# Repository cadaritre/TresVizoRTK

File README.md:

# TresVizoRTK

**Alimentación — 02/10/2026:** LiPo 1S 3.7 V / 3000 mAh confirmada. Lectura MAX17048 y apagado coordinado Mk2 implementados; falta identificar el elevador de 5 V y validar físicamente el conjunto con UM980. Ver `hardware/wiring.md` desde la raíz. La carga es autónoma por hardware; USB impide el corte total de batería.
TresVizoRTK es un proyecto personal para desarrollar un prototipo funcional de receptor GNSS RTK de triple banda con IMU y lector microSD, orientado a trabajos de topografía. El repositorio reunirá el firmware de un ESP32-S3, una aplicación móvil, la documentación electrónica, la lista de materiales y los archivos mecánicos de una carcasa imprimible en 3D. La cobertura de bandas del conjunto receptor y antena deberá verificarse con el hardware real.

El objetivo es disponer de un software de instrumento robusto en el ESP32-S3, tomando la experiencia de equipos Emlid como referencia de producto. El firmware concentrará la configuración y operación del equipo; una app independiente, todavía sin iniciar, resolverá levantamientos, replanteos y trazo. Esta referencia no implica equivalencia de funciones o rendimiento validada.

El objetivo de desarrollo es alcanzar aproximadamente 2 cm de precisión en condiciones favorables. Esa cifra no representa una capacidad implementada, medida ni garantizada. La operación bajo árboles es un interés de investigación del proyecto y tampoco implica una garantía de precisión bajo vegetación.

## Estado actual

El firmware **0.8.0** está adaptado y compilado para **SparkFun Thing Plus ESP32-S3 WRL-24408**. El equipo conserva el nombre **MeridianV**, el panel, BLE, NTRIP y los servicios GNSS. La nueva placa sustituye a la Tiny; las pruebas físicas históricas de esa placa no validan este montaje.

Esta entrega añade OLED SSD1306 I2C de 128×64, microSD integrada por SDIO y una identidad de hardware independiente para las imágenes firmadas. La pantalla muestra calidad GNSS, satélites, correcciones, grabación e IP; caduca la calidad cuando dejan de llegar datos. La tarjeta no se formatea automáticamente.

El panel identifica la placa, muestra el estado de OLED y microSD y controla el registro según la disponibilidad real y el cierre de archivos. Las descargas incompletas conservan `.part`. Cargador USB y diagnóstico BLE actualizados para la nueva placa; [detalle del software](docs/panel-campo.md).

El almacenamiento se llama **Memoria interna del dispositivo** en la interfaz y en las etiquetas de la API para aplicaciones; en la OLED, **MEM INT.**. El soporte físico sigue documentado como microSD. Grabación, cierre, catálogo y descarga implementados; comprobación física pendiente.

**Pendiente de banco:** primera carga en Thing Plus, OLED recibida, microSD, enlace UART y operación prolongada. La adaptación no cargó firmware en ningún equipo. **Encendido/apagado con el SparkFun Soft Power Switch implementado; prueba física pendiente.** Durante el banco, Thing Plus y UM980 mantienen alimentación USB separada y GND común.

**Sin integrar:** IMU, radio UHF y aplicación móvil. La carcasa diseñada para Tiny requiere revisión para la Thing Plus y la OLED; no se ha dado por compatible ni se ha regenerado CAD.

El [cableado vigente](hardware/wiring.md) reúne los pines y la primera instalación. Detalle de cambios y pruebas en el [README del firmware](firmware/esp32/README.md). Las imágenes OTA llevan la [firma del propietario](tools/firmware_signing/README.md).

## Alcance previsto

El prototipo busca llegar a:

- Operación como rover RTK o como base.
- Recepción y transmisión de correcciones por los enlaces que se validen.
- Acceso a correcciones NTRIP.
- Registro de observaciones GNSS para postproceso externo.
- Integración GNSS/IMU y compensación de inclinación del jalón, todavía por desarrollar y validar.
- Configuración y operación del instrumento gestionadas por el firmware del ESP32-S3.
- Aplicación móvil independiente para levantamientos, replanteos y trazo, con acceso a configuración y estado mediante el protocolo del instrumento.
- Registro de diagnósticos para análisis y mejora del sistema.

## Arquitectura resumida

- **Receptor GNSS:** calcula la solución GNSS/RTK y produce observaciones y mensajes compatibles con su modelo y firmware.
- **ESP32-S3:** controla el receptor, enruta RTCM, adquiere la IMU, gestiona tiempos, almacenamiento, comunicaciones y apagado seguro. La fusión GNSS/IMU es trabajo futuro.
- **IMU BMI088:** aporta aceleración y velocidad angular para la futura integración GNSS/IMU y compensación de inclinación.
- **Lector y tarjeta microSD:** proporcionan almacenamiento local de observaciones, datos IMU y diagnósticos bajo control del ESP32-S3.
- **Aplicación móvil independiente:** gestiona mapas, proyectos, levantamientos, replanteos, trazo e intercambio de archivos; consulta el estado y solicita cambios de configuración al firmware.

La aplicación se comunicará mediante un protocolo propio del instrumento, separado de los comandos específicos de Unicore o u-blox. BLE se prevé como enlace principal de control y telemetría; el objetivo de 20 Hz está pendiente de pruebas. Wi-Fi, conectado al hotspot del teléfono, permitiría al ESP32 acceder a NTRIP. USB se reserva para desarrollo y diagnóstico, y Wi-Fi o USB para transferencias grandes.

La [arquitectura](docs/architecture.md) describe las responsabilidades y los flujos de datos con mayor detalle.

## Hardware previsto

La base considerada incluye:

- Unicore UM980 en una placa de desarrollo o carrier como GNSS principal.
- u-blox ZED-F9P disponible para posibles pruebas.
- SparkFun Thing Plus ESP32-S3 WRL-24408, con 4 MB de flash y 2 MB de PSRAM Quad según fabricante.
- Bosch BMI088 en breakout.
- Socket microSD integrado de la Thing Plus, SDIO de cuatro bits y tarjeta FAT32.
- OLED Tecneu 0.96 pulgadas I2C, cuatro pines y 128×64; driver SSD1306 según referencia del vendedor.
- Antena Helix, cuya compra confirmó el propietario; modelo y bandas por verificar. La HA-901A mencionada inicialmente no está confirmada.
- Batería LiPo de una celda, nominal 3.7 V y 3000 mAh, confirmada por el propietario.
- SparkFun Soft Power Switch JST 2 mm comprado; integración de encendido/apagado implementado; prueba física pendiente.
- Carcasa cilíndrica impresa en 3D y montaje sobre jalón.

El enlace GNSS usa RX del ESP32 en **GPIO44** y TX en **GPIO43**, con GND común; ambos equipos reciben alimentación USB por separado. La OLED usa **SDA8/SCL9 y 3.3 V**. El pinout de la Tiny (18/17) queda como historial. La disponibilidad de PPS en la carrier UM980 concreta está pendiente de verificación. Consulta la [lista de materiales](hardware/bom.md) y el [cableado vigente](hardware/wiring.md).

## Mapa del repositorio

| Ruta | Contenido previsto |
| --- | --- |
| `firmware/esp32/` | Firmware del controlador ESP32-S3. |
| `app/` | Aplicación móvil del instrumento. |
| `hardware/` | BOM, módulos comerciales, conexiones y referencias del hardware vigente. |
| `mechanical/` | V1 para imprimir y fuentes necesarias para regenerarla. |
| `docs/` | Arquitectura, estado, hoja de ruta y entorno de desarrollo. |
| `tools/` | Puente USB, diagnóstico GNSS/BLE, empaquetado y actualización de firmware. |
| `tests/fixtures/` | Datos de prueba pequeños y anonimizados. |

## Documentación

- [Arquitectura del sistema](docs/architecture.md)
- [Estado del proyecto](docs/project-status.md)
- [Servicios actuales del ESP32 (0.5.0)](docs/esp32-services.md)
- [Configuración avanzada del receptor (0.6.0)](docs/gps-advanced.md)
- [Panel reorganizado para campo (0.6.0)](docs/panel-campo.md)
- [Hoja de ruta](docs/roadmap.md)
- [Entorno y prácticas de desarrollo](docs/development.md)
- [Lista de materiales](hardware/bom.md)
- [Identificación del hardware recibido](hardware/identification.md)
- [Interfaces y conexiones](hardware/wiring.md)
- [Mecánica vigente, V2.2](mechanical/README.md)
- [Auditoría de la carcasa V1](mechanical/AUDITORIA-V1.md)
- [BOM de tornillería](mechanical/v2.2/SCREW-BOM.md)
- [Revisión de integración de V1, antecedente](docs/INTEGRATION_REVIEW.md)

No se ha seleccionado una licencia. El contenido del repositorio no debe interpretarse como publicado bajo una licencia específica hasta que el propietario la defina expresamente.

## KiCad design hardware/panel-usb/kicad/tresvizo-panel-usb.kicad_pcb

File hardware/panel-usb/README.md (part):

# Placa del USB-C del panel (TresVizo MeridianV, exploratoria v0.1)

> **En la v0.3 (rama `hw/compact-v03`) esta placa no se usa:** el USB-C va en la placa principal
> ([../main-board](../main-board/README.md)).

> **Estado:** diseño generado con scripts y revisado con el ERC y el DRC de KiCad 10.0.6.
> **No se ha fabricado ni probado.** Vive en la rama `hw/main-board-kicad`, junto a la placa principal
> ([../main-board](../main-board/README.md)), y se pide en el mismo panel de JLCPCB que ella.

## Para qué sirve

Lleva un receptáculo USB-C 2.0 al ras de la cara exterior de la tapa curva del panel de la carcasa
V2.2 y lo une con un cable corto JST GH de 8 pines a J101 de la placa principal (carga a 5 V y
USB nativo del ESP32-S3). Es una placa de 4 capas y 1.6 mm, con todas las piezas por la cara superior.

Esquema en [fab/tresvizo-panel-usb-schematic.pdf](fab/tresvizo-panel-usb-schematic.pdf) y vistas en
[fab/tresvizo-panel-usb-top.png](fab/tresvizo-panel-usb-top.png) /
[fab/tresvizo-panel-usb-bottom.png](fab/tresvizo-panel-usb-bottom.png). Los genera `build.py`, igual que el ZIP
de Gerber: cambian en cada vuelta y solo se guardan en git en los hitos (`git add -f`).

## Circuito

| Ref. | Pieza | Función |
| --- | --- | --- |
| J501 | HRO TYPE-C-31-M-12 (USB-C 16 contactos, horizontal) | A6/B6 = D+ y A7/B7 = D− unidos en la placa; SBU sin conectar; carcasa a GND |
| R501, R502 | 5.1 kΩ 0402 | Rd de CC1 y CC2 a GND: el cargador ve un sumidero y entrega 5 V |
| U501 | USBLC6-2SC6 (UMW) | ESD de D+/D−; pin 5 a VBUS y pin 2 a GND |
| D501 | SMF15A (SOD-123FL) | TVS unidireccional de VBUS (la misma pieza que usa la placa principal) |
| J502 | JST GH 8 lateral, XUNPU WAFER-GH1.25-8PWB | Cable a J101 de la placa principal |

Redes: VBUS, GND, USB_DP, USB_DN, CC1, CC2. VBUS se queda en 5 V: solo hay Rd (sin PD) y el cargador
BQ25798 de la placa principal no tiene conectados sus D+/D− (sin HVDCP), así que el pin 5 del USBLC6
puede ir a VBUS.

Detalles de la placa:

- **Cruce de D+/D−.** En el receptáculo los contactos quedan D+, D−, D+, D− (B6, A7, A6, B7). D+ se une
  por la capa superior con una U que rodea la vía de A7; D− se une por la capa inferior y vuelve arriba
  debajo de la U. Desde ahí el par va a 0.25 mm con 0.2 mm entre pistas.
- **U501 cerca de J502.** D+ atraviesa el USBLC6 (pin 6 → pin 1, bajo el cuerpo) y entra a J502.8; D− le
  llega con un ramal de unos 4.5 mm por la capa inferior. Entre J501 y U501 hay unos 10 mm de pista:
  junto al receptáculo no cabía con el cruce, las Rd y VBUS. La placa principal tiene su propio USBLC6
  (U101) junto a J101.
- **VBUS (≥ 0.6 mm).** Cada pad de VBUS del USB-C baja por dos vías a una pista de 0.8 mm en la capa
  inferior, que sube por tres vías a los pines 1-3 de J502. D501 va junto a J502.1. Así VBUS cruza por
  debajo del par de datos sin cortar nada.
- **GND.** Rellenos de GND en las cuatro capas (las internas enteras), 18 vías de cosido y 9 vías de
  bajada de pads (fanout). Los pads de GND del USB-C y las Rd van directo a las patas de la carcasa.
  Todas las vías van tapadas por las dos caras.

## Elección del receptáculo

Se compararon los planos de los dos candidatos (stock de la API de JLCPCB del 04-10-2026):

| | HRO TYPE-C-31-M-12 (C165948) | SHOU HAN TYPE-C 16PIN 2MD(073) (C2765186) |
| --- | --- | --- |
| Stock / precio unitario | 424 026 / 0.19 USD | 882 909 / 0.07 USD |
| Valores nominales | 20 V, 5 A | 5 V, 3 A |
| Canto de la placa | **Dibujado** («PCB EDGE»): 5.79 mm por delante de los postes de centrado | No lo da: su «PRODUCT EDGE» es el frente del propio conector |
| Cara de acoplamiento | 6.28 mm por delante de los postes (2.60 mm por delante de las patas delanteras) → **sobresale 0.49 mm** del canto dibujado | 6.28 mm por delante de los postes; sin referencia al canto |
| Altura del eje | No acotada; altura total 3.26 mm | No acotada; altura total 3.16 mm |

Se eligió el **HRO TYPE-C-31-M-12**: su plano fija la cara respecto del canto. Ningún plano acota la
altura del eje. El modelo 3D de LCSC tiene la carcasa de 0.05 a 3.25 mm sobre la placa, lo que pone el
eje a **1.65 mm**. Concuerda con la altura total de 3.26 mm del plano y con la vista frontal medida a
escala (1.65-1.69 mm).

La huella sale de LCSC/EasyEDA (orientación de JLCPCB), con estos ajustes (ver `scripts/mklib.py`):

- pads dobles separados por contacto;
- ranuras de la carcasa con las medidas del plano (0.6 × 1.7 y 0.6 × 1.4 mm), anillo de 0.2 mm y pasta;
- postes de centrado sin metalizar;
- modelo 3D corrido 2.22 mm, porque el de EasyEDA quedaba fuera de sus ranuras (comprobado en la
  exportación VRML).

## Mecánica

Ejes de la carcasa V2.2 (del estudio CAD): z = eje del jalón hacia arriba, +Y hacia el panel, +X a la
izquierda mirando el panel. La placa es horizontal: cara inferior en z = 90.17 y cara de componentes en
z = 91.77, hacia arriba. Coordenadas de la placa, vista desde arriba con el USB-C arriba:
**u = x + 10.4**, **v = 31.3 − y**.

- **Contorno:** cuerpo u 0–20.8, v 4.7–19.8; lengüeta frontal u 5.2–15.6, v **0.89**–4.7; esquinas de
  R0.5.
  - **El USB-C sobresale 1.29 mm** del frente de la lengüeta (decisión del propietario del
    05-10-2026). El frente quedó 0.8 mm más atrás que el canto del plano de HRO: v = 0.89
    (y = 30.41). La cara sigue en v = −0.40.
  - El cobre más cercano al frente es el de las ranuras delanteras de la carcasa del USB-C, a
    0.41 mm (la regla pide 0.3 mm). Los rellenos de GND paran a 0.3 mm.
  - Los agujeros no cambian: están en el cuerpo, a 0.5 mm de su canto delantero (v 4.7) y a 1.4 mm
    de los laterales.
- **J501:** centrado en u = 10.4 (x = 0), **cara en v = −0.40 (y = 31.70)**, a ras de la tapa curva.
  **Eje a 1.65 mm de la cara de componentes → z = 93.42** (el estudio buscaba 93.50; la abertura de la
  tapa está centrada en z = 93.2 con ±3.5 mm). Carcasa de x = ±4.47, z 91.82–95.02.
- **Agujeros:** H501 y H502, M2 sin metalizar de Ø2.2 en (u, v) = (2.5, 6.3) y (18.3, 6.3), es decir
  x = ∓7.9, y = 25.0, sin cobre en Ø4.4.
- **J502 (GH 8):** en el canto trasero con la boca hacia −Y. Pines 1-8 de izquierda a derecha (u 6.02 a
  14.77), pads en v 14.07–15.77, cuerpo en v 15.5–19.5 y 4.35 mm de alto (llega a z = 96.12).
  - Los anclajes llegan hasta v 19.48 para dejar 0.3 mm de cobre al canto.
  - El plano de XUNPU pone el frente del cuerpo a ras del extremo de los anclajes, y el modelo 3D de
    LCSC 0.09 mm más afuera: la boca queda 0.23–0.32 mm dentro del canto.
  - El GH original de JST dibuja los anclajes 0.25 mm por delante del cuerpo.
- **Resto de piezas:**

  | Ref. | (u, v) | Por qué |
  | --- | --- | --- |
  | R501 | (14.0, 9.75) | Dentro de la zona prevista |
  | R502 | (6.8, 9.75) | Dentro de la zona prevista |
  | U501 | (17.1, 13.4) | Fuera de la zona: con el GH los pads de J502 empiezan en v = 14.07 y queda sitio debajo |
  | D501 | (3.4, 13.0) | Fuera de la zona, junto a J502.1 |

  Todo queda a más de 1 mm de los agujeros (la zona sin cobre es de Ø4.4) y de los cantos laterales.
- **Puentes del panel:** uno en cada canto lateral (u = 0 y u = 20.8), centrados en v = 16.0, de 5 mm.
  - Medido desde la esquina superior izquierda del rectángulo que encierra la placa (u 0, v 0.89):
    **canto izquierdo y canto derecho, a 15.11 mm**.
  - Zona sin cobre de 1 mm de fondo en v 13.0–19.0.
  - El canto trasero no sirve: allí están la boca y los anclajes de J502.
  - En el panel, el USB-C asoma 1.29 mm sobre la fresa. Con la fresa normal de 2 mm quedaría a
    0.71 mm del marco. Por eso, frente a la lengüeta, la fresa del panel se ensancha a 3 mm y quedan
    **1.71 mm** (`cuts` en `../main-board/kicad/panel.json`).

`fab/check3d.txt` (lo escribe `build.py`) mide estas posiciones sobre los modelos 3D de la placa armada.

### Cambios que necesita la tapa del panel del V2.2 (solo propuesta; no se tocó el CAD)

- Quitar el bolsillo del JST-XH.
- Abrir un hueco de 12.8 × 7.0 mm con radios de 1.2 mm, centrado en x = 0, z = 93.2.
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
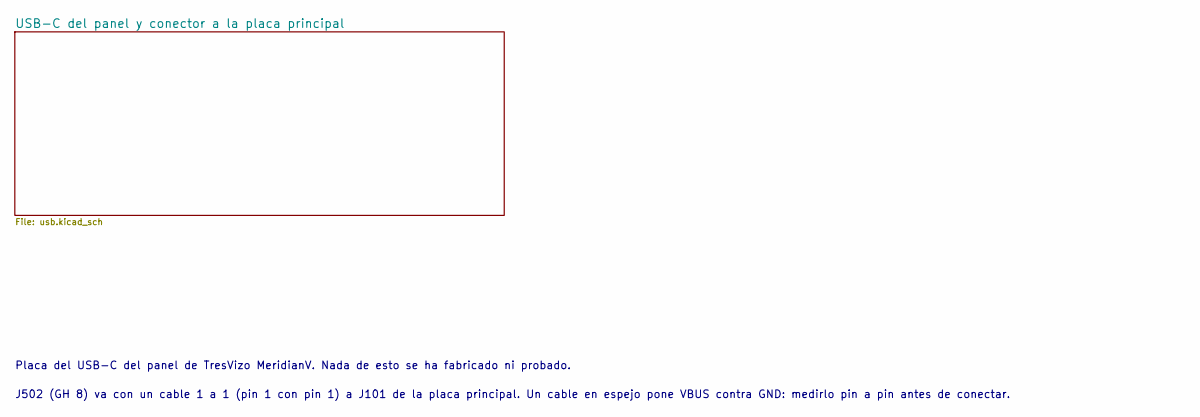
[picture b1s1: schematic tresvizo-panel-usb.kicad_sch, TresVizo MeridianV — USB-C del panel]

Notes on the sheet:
Placa del USB-C del panel de TresVizo MeridianV. Nada de esto se ha fabricado ni probado.
J502 (GH 8) va con un cable 1 a 1 (pin 1 con pin 1) a J101 de la placa principal. Un cable en espejo pone VBUS contra GND: medirlo pin a pin antes de conectar.

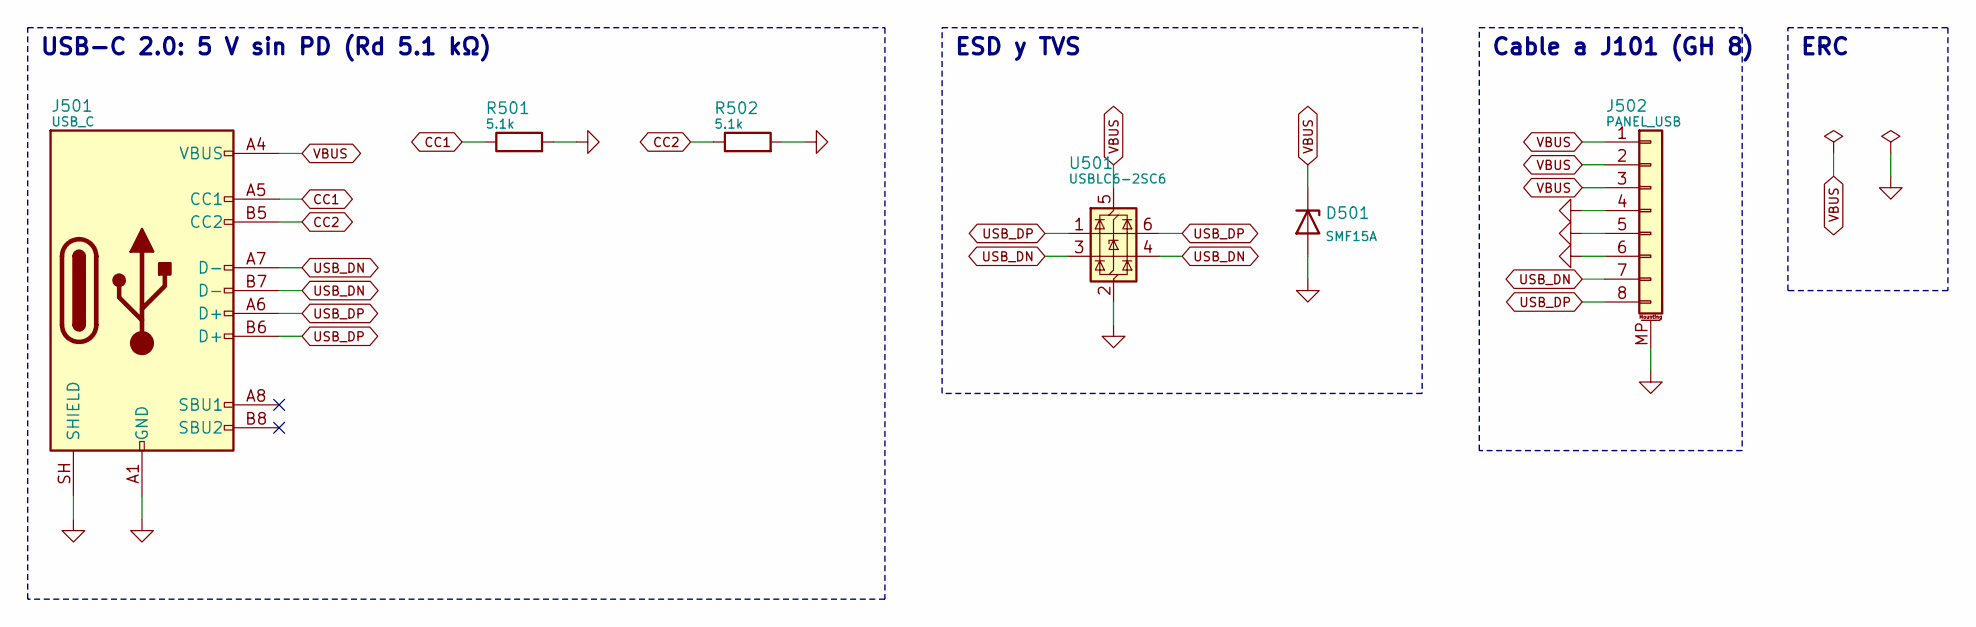
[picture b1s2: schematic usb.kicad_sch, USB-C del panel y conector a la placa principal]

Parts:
D501: SMF15A; SOD-123FL_L2.7-W1.8-LS3.8-RD; MPN SMF15A; LCSC C19077509
J501: USB_C; USB-C_SMD-TYPE-C-31-M-12; MPN TYPE-C-31-M-12; LCSC C165948
J502: PANEL_USB; CONN-SMD_8P-P1.25_XUNPU-WAFER-GH1.25-8PWB; MPN WAFER-GH1.25-8PWB; LCSC C3029383
R501, R502: 5.1k; R_0402_1005Metric; MPN 0402WGF5101TCE; LCSC C25905
U501: USBLC6-2SC6; SOT-23-6_L2.9-W1.6-P0.95-LS2.8-BL; MPN USBLC6-2SC6; LCSC C2687116

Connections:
CC1: J501.A5 (CC1), R501.1
CC2: J501.B5 (CC2), R502.1
GND: D501.2 (A), J501.A1 (GND), J501.A12 (GND), J501.B1 (GND), J501.B12 (GND), J501.SH (SHIELD), J502.4, J502.5, J502.6, J502.MP (MountPin), R501.2, R502.2, U501.2 (GND)
USB_DN: J501.A7 (D-), J501.B7 (D-), J502.7, U501.3 (I/O2), U501.4 (I/O2)
USB_DP: J501.A6 (D+), J501.B6 (D+), J502.8, U501.1 (I/O1), U501.6 (I/O1)
VBUS: D501.1 (K), J501.A4 (VBUS), J501.A9 (VBUS), J501.B4 (VBUS), J501.B9 (VBUS), J502.1, J502.2, J502.3, U501.5 (VBUS)

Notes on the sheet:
USB-C 2.0: 5 V sin PD (Rd 5.1 kΩ)
ESD y TVS
Cable a J101 (GH 8)
ERC

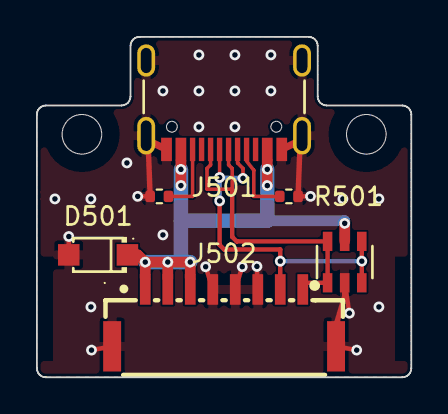
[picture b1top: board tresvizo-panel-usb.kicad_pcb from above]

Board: 4 copper layers, 20.8 x 18.9 mm, 8 parts (0 on the bottom side), 6 nets.

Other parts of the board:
H501, H502: MountingHole_2.2mm_M2

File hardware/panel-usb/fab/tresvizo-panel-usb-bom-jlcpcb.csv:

Comment,Designator,Footprint,LCSC Part #
SMF15A,D501,SOD-123FL_L2.7-W1.8-LS3.8-RD,C19077509
USB_C,J501,USB-C_SMD-TYPE-C-31-M-12,C165948
PANEL_USB,J502,CONN-SMD_8P-P1.25_XUNPU-WAFER-GH1.25-8PWB,C3029383
5.1k,"R501,R502",R_0402_1005Metric,C25905
USBLC6-2SC6,U501,SOT-23-6_L2.9-W1.6-P0.95-LS2.8-BL,C2687116

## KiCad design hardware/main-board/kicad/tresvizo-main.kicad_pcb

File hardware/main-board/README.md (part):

# Placa principal TresVizo MeridianV (exploratoria, v0.3 compacta)

> **Estado:** diseño generado con scripts y revisado con el ERC y el DRC de KiCad 10.0.6 y con una
> auditoría eléctrica independiente (08-10-2026), cuyos cambios ya están aplicados. **No se ha
> fabricado ni probado.** Vive en la rama `hw/compact-v03`, fuera de `main`, porque el propietario la
> pidió como exploración (07-10-2026). Los resultados de las comprobaciones están en
> [Verificaciones](#verificaciones).
>
> La v0.2 (placa de 46 × 64 mm más la panel-usb, para la carcasa V2.3) sigue en la rama
> `hw/main-board-kicad`.

La v0.3 es la versión compacta del receptor. Mantiene el concepto de la v0.2: el UM980 en su
carrier BDLX, por cable, y el ESP32-S3-WROOM-1 en la placa. Pero va en un tubo de **Ø56 × 116** con
una cara plana al frente ([carcasa V3.0](../../mechanical/v3.0/README.md)). La placa mide
**36 × 71.5 mm** (4 capas, 1.6 mm, componentes solo por la cara de arriba) y lleva lo que en la v0.2
iba en el panel: el USB-C, la OLED (soldada a la placa), un pulsador y un LED de estado. El BMI088
vuelve a la placa. No hay panel-usb: la placa se pide sola, en un panel de JLCPCB con un BOM y un
CPL. La batería pasa a un pack comercial 1S2P de dos 18650.

| Bloque | Pieza | Notas |
| --- | --- | --- |
| GNSS | Carrier BDLX RTK_UM98_V1.0.1, fuera de la placa | J301 (SH de 8 pines): COM2 a 115200, PPS, EVENT, RESET_N y su 5 V. Arnés soldado a la carrier |
| 5 V del GNSS | TI TPS63070 (buck-boost) | 4.88 V desde VSYS; GPIO45 lo enciende; apagado desconecta la carga |
| MCU | ESP32-S3-WROOM-1-N16R2 | 16 MB de flash y 2 MB de PSRAM quad. Antena hacia el canto −X. Mismos GPIO que la v0.2, salvo GPIO48 (ver [Firmware](#firmware-qué-tiene-que-cambiar)) |
| IMU | Bosch BMI088 en la placa (U401) | I2C en un segundo bus (GPIO41/42), INT1 en GPIO2 e INT3 en GPIO1; 0x18 y 0x68 |
| Registro | microSD de empuje TF-015 (J401), SD_MMC 4 bits | CLK GPIO6, CMD 7, D0 5, D1 4, D2 16, D3 15 y detección en 17 (HIGH con tarjeta). Boca hacia el costado +X |
| USB-C | HRO TYPE-C-31-M-12 (J101) | Rd de 5.1 kΩ en CC1 y CC2, TVS SMF15A en VBUS y USBLC6 (U101) en D+/D−. Boca hacia el costado +X |
| Carga | TI BQ25798 (buck-boost NVDC) | USB-C a 5 V, techo de entrada ~1.45 A (ILIM); 1S; usar y cargar a la vez. Carga de 1 A por omisión; el firmware no debe pasar de 1.5 A |
| Apagado | Modo *ship* del cargador + FET externo | El pulsador despierta la placa (QON) |
| 3.3 V | TI TPS62903 | 3–17 V, 3 A, modo 100 % |
| Medidor | MAX17048 | I2C 0x36 |
| Interfaz | OLED 0.96" de 4 pines (J403), pulsador SW401 y LED rojo D403 | La OLED es la del propietario y la suelda él sobre pads SMD. El LED va en GPIO48 |
| Batería | Pack 1S2P (2 × 18650 en paralelo) por J102 (GH de 4 pines) | NTC 10k B3435 obligatoria por J404 (SH de 2 pines) |

Esquema en [fab/tresvizo-main-schematic.pdf](fab/tresvizo-main-schematic.pdf), mapa de pines y
conectores en [fab/pinout.md](fab/pinout.md) y vistas en `fab/*-top.png` / `fab/*-bottom.png`. La
especificación de la v0.3, la colocación, las desviaciones, el ruteo y la auditoría eléctrica están
en [research/v03-compacta.md](research/v03-compacta.md); la investigación de la v0.2, en
[research/v02.md](research/v02.md). El esquema en PDF, las vistas y los Gerber los genera
`build.py` y solo se guardan en git en los hitos (ver [Regenerar](#regenerar)).

## Decisiones

### De la v0.3 (07-10-2026 y auditoría del 08-10-2026)

Pedido del propietario: un receptor más chico, con el panel dentro de la placa principal, dos 18650
y la carrier tal cual. Lo que resultó al aplicarlo, con su motivo:

1. **Tubo de Ø56 × 116 y placa de 36 × 71.5 mm.** Unos dos tercios del volumen de V2.3.
   - Empezó en Ø52 × 100. El endurecimiento del 08-10-2026 lo agrandó para dejar holguras de
     impresión y de montaje, y el coaxial con curvas de R 12 o más (ver [Mecánica](#mecánica)); la
     placa no cambió de lugar.
   - Los cantos laterales corren por los rieles del chasis, con una franja de 1 mm sin componentes.
   - Componentes solo por la cara de arriba: el dorso mira a la carrier a 0.5 mm.
   - El alto de cada pieza lo limitan la curva del tubo y la cara plana.
   - Dos muescas en el contorno: la clavija del SMA de la carrier y la funda de la clavija del USB-C.
   - Ver [Mecánica](#mecánica).
2. **El panel entra en la placa.** Motivos: no hay cables al panel y el botón metálico de 12 mm de
   la v0.2 es difícil de conseguir.
   - USB-C J101 (TYPE-C-31-M-12, C165948, el de la panel-usb): Rd de 5.1 kΩ en CC1 y CC2 (R119,
     R120), TVS SMF15A en VBUS y USBLC6 (U101) junto al conector.
   - Pulsador táctil SW401 (TS-1187A-B-A-B, 5.1 × 5.1 × 1.5 mm) a BTN_N: despierta al cargador (QON)
     y llega a GPIO18 por D402. Conserva la ESD D401, porque la tecla deja llegar descargas a su botón
     de latón.
   - LED de estado D403 (0603 rojo) directo desde GPIO48, con 330 Ω: unos 4.4 mA. Con 1 kΩ quedaba
     tenue detrás de la guía de luz (auditoría). R409 era la resistencia del anillo del botón.
   - Se van J101 GH 8 (USB del panel), J402 (botón), J405 (IMU por cable), Q402 y R410 (anillo del
     botón). J403 sigue, ahora como huella del módulo OLED. Los números R106 y R410 quedan sin usar,
     para no renumerar.
3. **OLED soldada a la placa (J403).** Es el mismo módulo I2C de 4 pines que ya tiene el propietario.
   - Va girado 180° (pines abajo), sobre separadores de 1.3 mm, con el vidrio detrás de la ventana de
     la cara plana. Sobresale por encima del canto de arriba de la placa.
   - **Pads SMD de 1.7 × 2.4 mm, sin agujeros** (auditoría). Detrás de la fila de pines está el SMA
     de la carrier, a 0.4 mm del dorso, y una soldadura pasante recortada podía cortocircuitar +3V3 y
     SCL con su carcasa (GND).
   - La única unión pasante de la placa son las cuatro patas de la carcasa del USB-C (GND), que no
     salen por detrás.
   - JLCPCB no monta la OLED: sus pads llevan pasta y salen estañados. El propietario corta los pines
     a la altura del separador y los suelda sobre los pads calentando desde el frente del módulo.
4. **BMI088 en la placa (U401)**, como en v0.1, en el bus que usaba J405. No hacen falta cable ni
   plataforma, y queda rígido con el resto del equipo.
   - Conexión según la hoja de Bosch (BST-BMI088-DS001 rev 1.9): PS a VDDIO (I2C), CSB1 a VDDIO y
     CSB2 al aire.
   - SDO1 y SDO2 a GND: acelerómetro 0x18 y giróscopo 0x68, las direcciones del breakout de la v0.2.
   - INT2 e INT4 sin conectar, 100 nF en VDD y en VDDIO, pull-ups de 4.7 kΩ y sin cobre de la cara
     de arriba bajo el encapsulado (DS §8.2).
   - Sigue en un **segundo bus** (GPIO41 SDA, GPIO42 SCL, 400 kHz), aparte del de la OLED, el
     cargador y el medidor, y con sus dos interrupciones.
   - Va en la esquina de abajo a la izquierda, lejos de L101, del botón y de los puentes del panel.
5. **Pack 1S2P por un GH 4 (J102).** El PH 2 lateral de la v0.2 mide 5.5 mm sobre la placa y aquí
   caben unos 4.6.
   - JST GH 4 lateral (SM04B-GHS-TB, C189895, unos 4.25 mm de alto) con dos contactos por polo: 1 y
     2 a GND, 3 y 4 a VBATT_IN.
   - JST da 1 A por contacto con cable AWG #26: unos 2 A por polo. El firmware limita la carga a
     1.5 A como mucho (ver [Firmware](#firmware-qué-tiene-que-cambiar)).
6. **Conectores de cable solo en el canto de abajo**, con la boca hacia abajo: a los lados no hay
   sitio para las clavijas. Son J404 (NTC), J102 (batería) y J301 (GNSS), y se alcanzan quitando la
   base.
7. **La carrier BDLX tal cual**, con el arnés soldado a sus filas de agujeros, como en la v0.2. Sus
   agujeros solo se conocen a ±1 mm (foto): una mezzanine pediría medidas exactas.
8. **Antena del ESP32 hacia el canto −X**, con un área sin pistas, vías ni rellenos en las cuatro
   capas que la auditoría amplió (ver
   [research/v03-compacta.md](research/v03-compacta.md#colocación)).
9. **Resto de la auditoría eléctrica** (detalle en
   [research/v03-compacta.md](research/v03-compacta.md#auditoría-eléctrica-08-10-2026)):
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
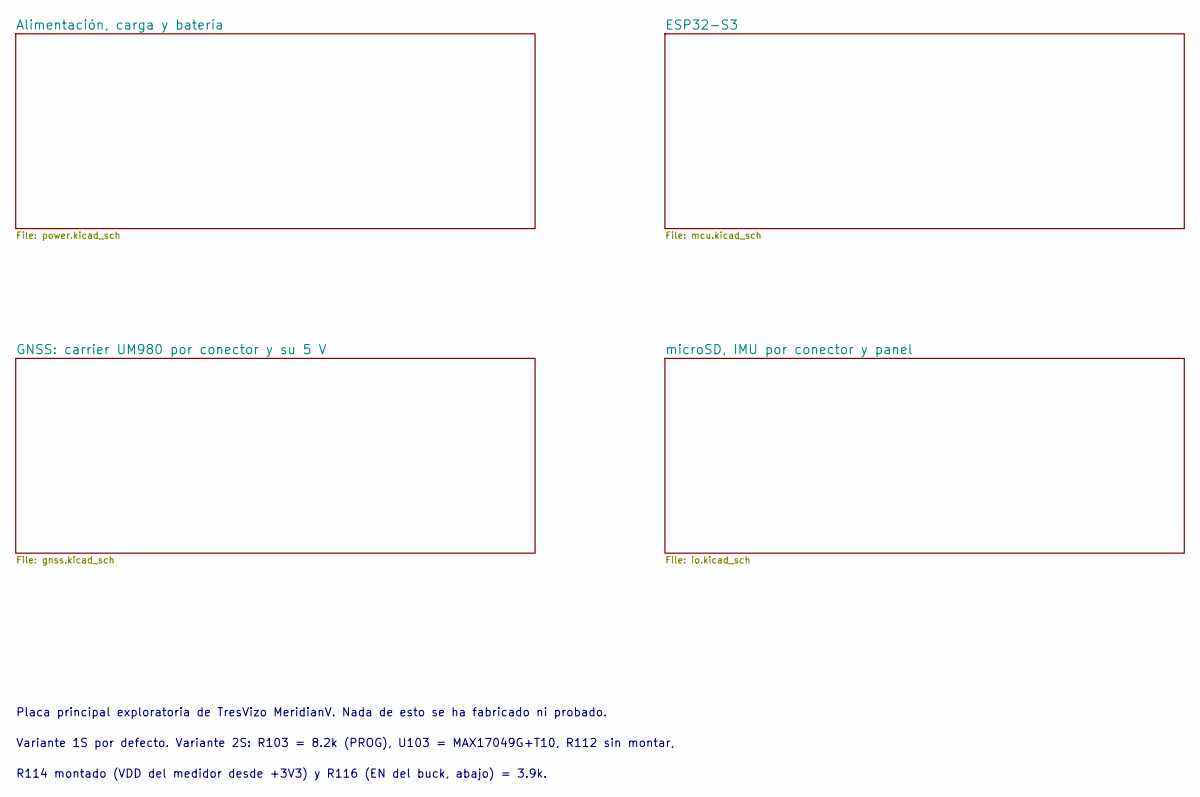
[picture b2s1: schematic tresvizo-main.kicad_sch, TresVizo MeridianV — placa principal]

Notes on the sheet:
Placa principal exploratoria de TresVizo MeridianV. Nada de esto se ha fabricado ni probado.
Variante 1S por defecto. Variante 2S: R103 = 8.2k (PROG), U103 = MAX17049G+T10, R112 sin montar,
R114 montado (VDD del medidor desde +3V3) y R116 (EN del buck, abajo) = 3.9k.

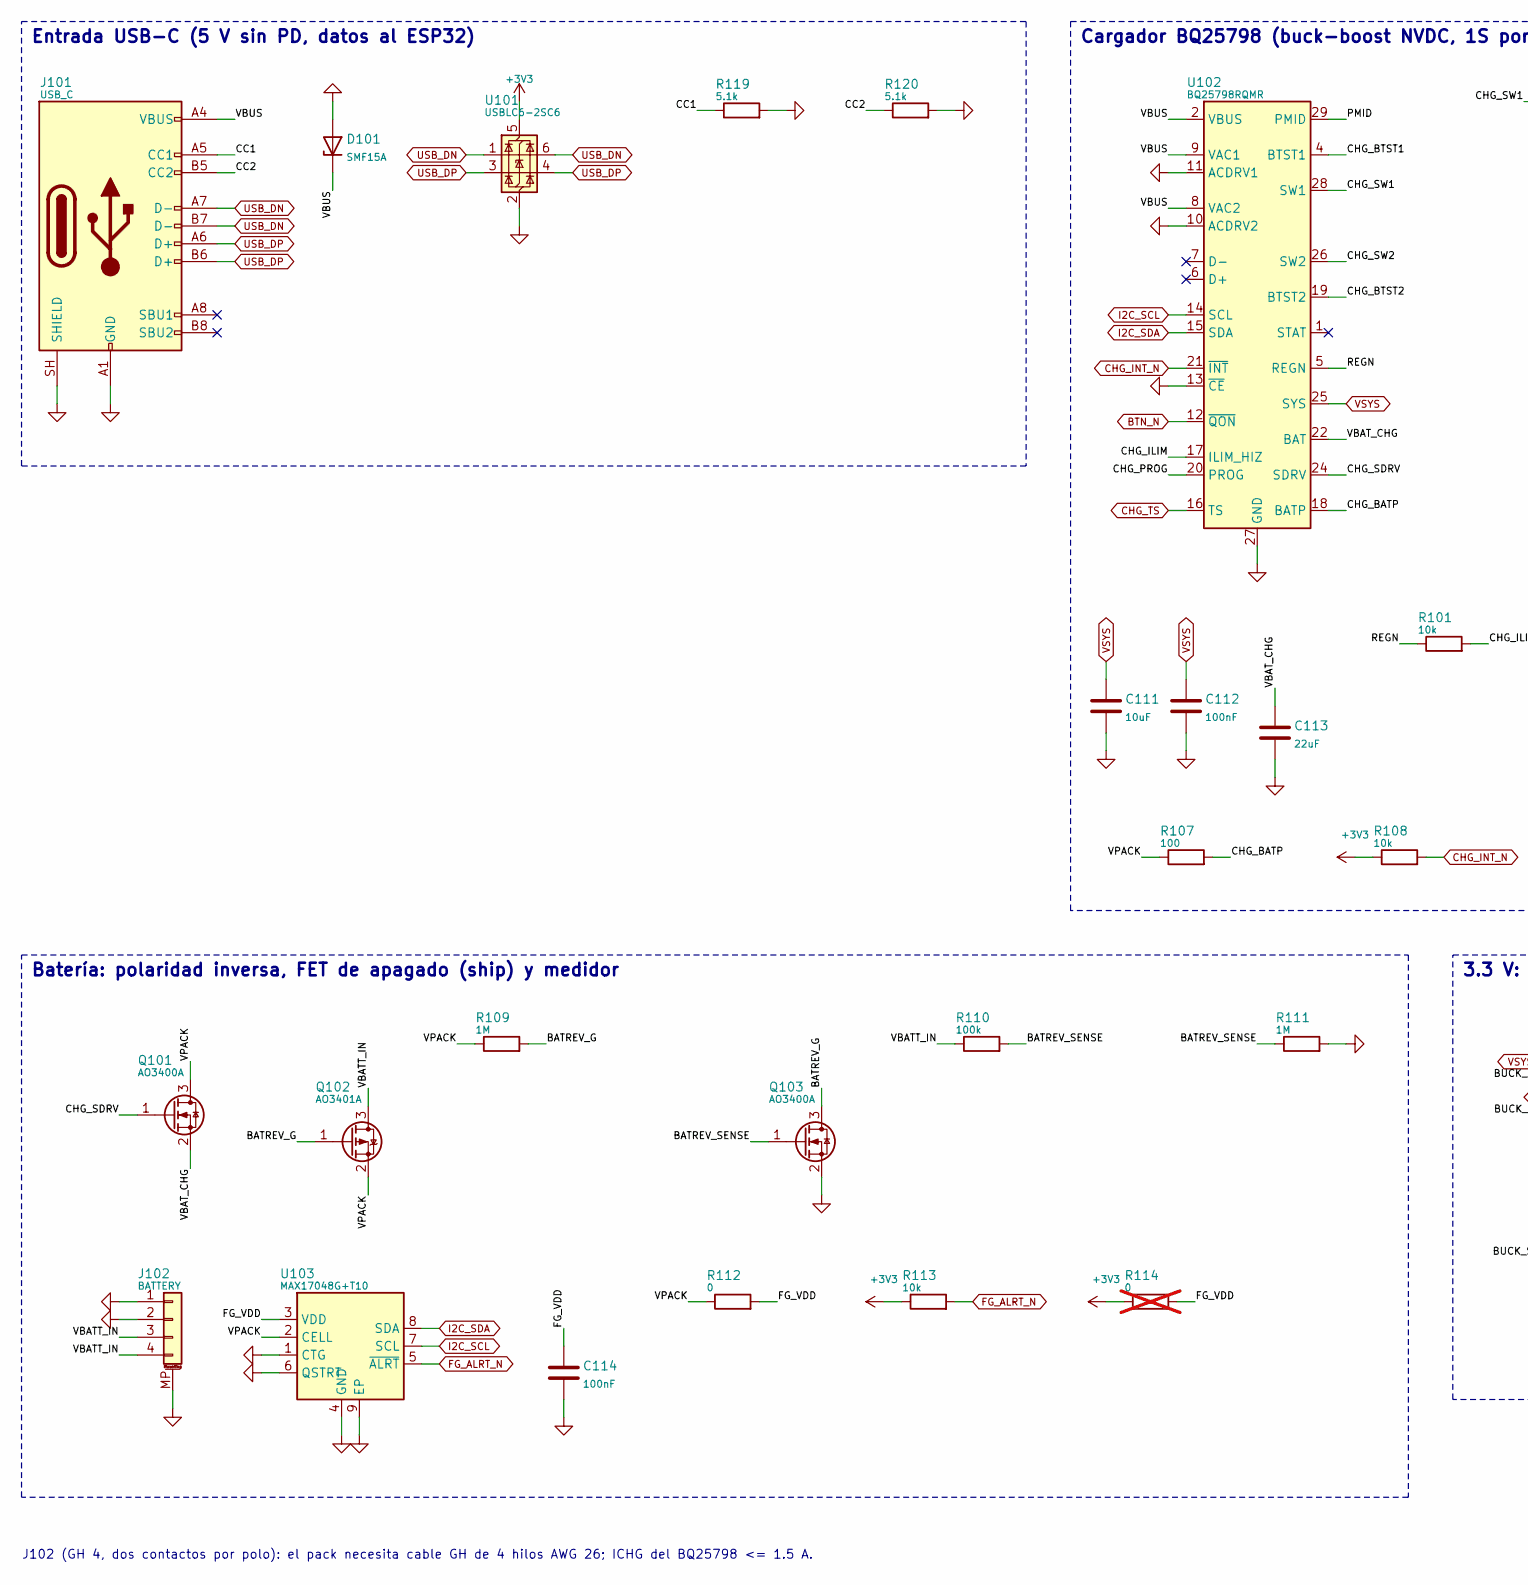
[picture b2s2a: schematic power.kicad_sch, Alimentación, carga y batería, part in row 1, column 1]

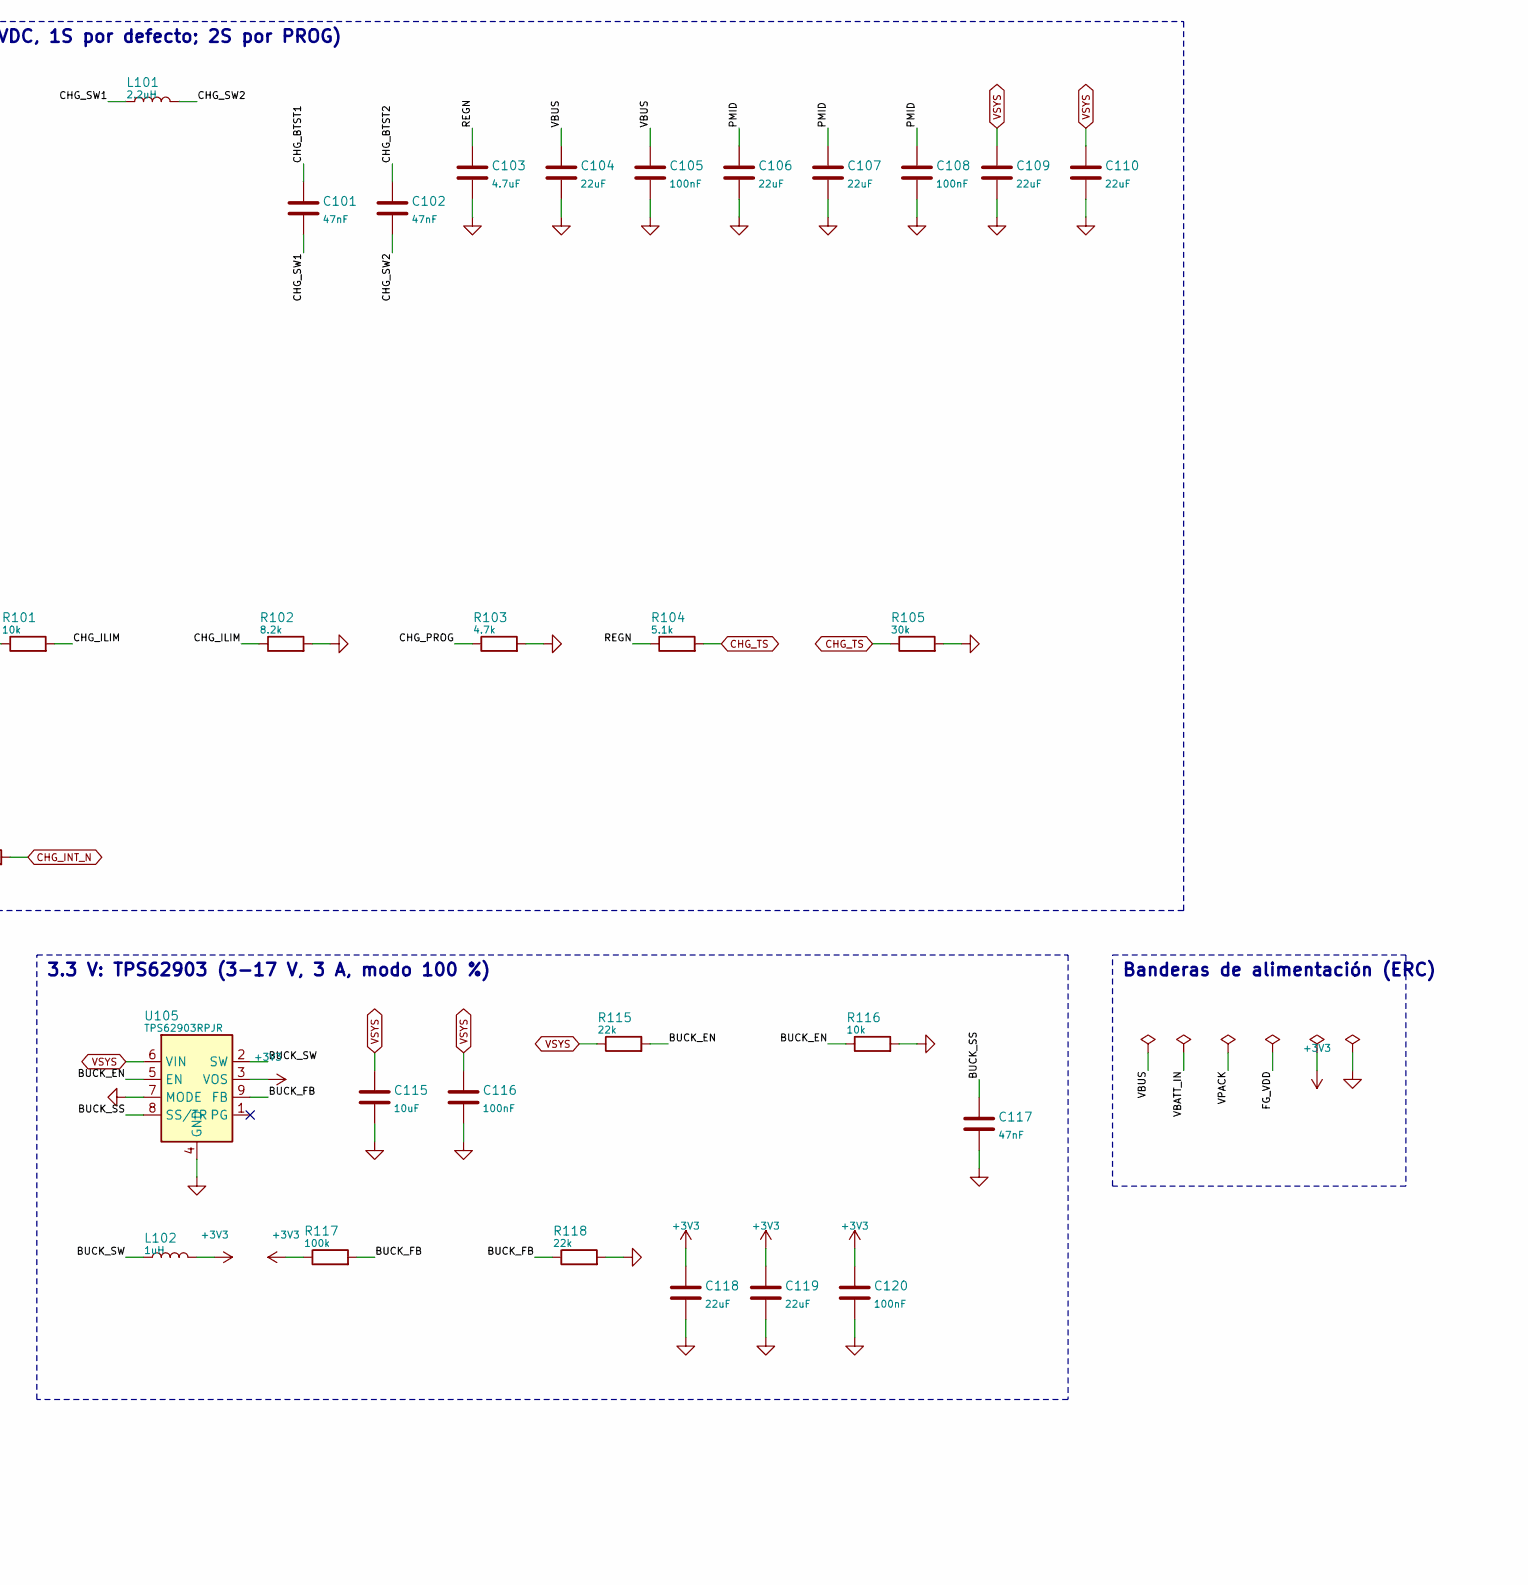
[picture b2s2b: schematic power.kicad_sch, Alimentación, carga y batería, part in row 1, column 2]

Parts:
C101, C102, C117: 47nF; C_0603_1608Metric; MPN CL10B473KB8NNNC; LCSC C1622
C103: 4.7uF; C_0603_1608Metric; MPN CL10A475KO8NNNC; LCSC C19666
C104, C106, C107, C109, C110, C113, C118, C119: 22uF; C_0805_2012Metric; MPN CL21A226MAQNNNE; LCSC C45783
C105, C108, C112, C114, C116, C120: 100nF; C_0402_1005Metric; MPN CL05B104KB54PNC; LCSC C307331
C111, C115: 10uF; C_0805_2012Metric; MPN CL21A106KAYNNNE; LCSC C15850
D101: SMF15A; SOD-123FL_L2.7-W1.8-LS3.8-RD; MPN SMF15A; LCSC C19077509
J101: USB_C; USB-C_SMD-TYPE-C-31-M-12; MPN TYPE-C-31-M-12; LCSC C165948
J102: BATTERY; CONN-SMD_4P-P1.25_SM04B-GHS-TB-LF-SN; MPN SM04B-GHS-TB(LF)(SN); LCSC C189895
L101: 2.2uH; IND-SMD_L5.4-W5.2; MPN MWSA0503S-2R2MT; LCSC C408408
L102: 1uH; L2520; MPN DFE252012F-1R0M=P2; LCSC C435392
Q101, Q103: AO3400A; SOT-23-3_L2.9-W1.3-P1.90-LS2.4-BR; MPN AO3400A; LCSC C20917
Q102: AO3401A; SOT-23_L2.9-W1.3-P1.90-LS2.4-BR; MPN AO3401A; LCSC C15127
R101, R108, R113, R116: 10k; R_0402_1005Metric; MPN 0402WGF1002TCE; LCSC C25744
R102: 8.2k; R_0402_1005Metric; MPN 0402WGF8201TCE; LCSC C25924
R103: 4.7k; R_0402_1005Metric; MPN 0402WGF4701TCE; LCSC C25900
R104, R119, R120: 5.1k; R_0402_1005Metric; MPN 0402WGF5101TCE; LCSC C25905
R105: 30k; R_0603_1608Metric; MPN 0603WAF3002T5E; LCSC C22984
R107: 100; R_0402_1005Metric; MPN 0402WGF1000TCE; LCSC C25076
R109, R111: 1M; R_0402_1005Metric; MPN 0402WGF1004TCE; LCSC C26083
R110, R117: 100k; R_0402_1005Metric; MPN 0402WGF1003TCE; LCSC C25741
R112: 0; R_0402_1005Metric; MPN 0402WGF0000TCE; LCSC C17168
R114: 0; R_0402_1005Metric; MPN 0402WGF0000TCE; LCSC C17168; not fitted
R115, R118: 22k; R_0402_1005Metric; MPN 0402WGF2202TCE; LCSC C25768
U101: USBLC6-2SC6; SOT-23-6_L2.9-W1.6-P0.95-LS2.8-BL; MPN USBLC6-2SC6; LCSC C2687116
U102: BQ25798RQMR; Texas_RQM0029A_VQFN-29_4x4mm_P0.4mm; MPN BQ25798RQMR; LCSC C2876593
U103: MAX17048G+T10; TDFN-8_L2.0-W2.0-P0.50-BL-EP1.2; MPN MAX17048G+T10; LCSC C2682616
U105: TPS62903RPJR; VQFN-HR-9_L2.0-W1.5-P0.50-TL; MPN TPS62903RPJR; LCSC C2866502

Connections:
/Alimentación, carga y batería/BATREV_G: Q102.1 (G), Q103.3 (D), R109.2
/Alimentación, carga y batería/BATREV_SENSE: Q103.1 (G), R110.2, R111.1
/Alimentación, carga y batería/BUCK_EN: R115.2, R116.1, U105.5 (EN)
/Alimentación, carga y batería/BUCK_FB: R117.2, R118.1, U105.9 (FB)
/Alimentación, carga y batería/BUCK_SS: C117.1, U105.8 (SS/TR)
/Alimentación, carga y batería/BUCK_SW: L102.1, U105.2 (SW)
/Alimentación, carga y batería/CC1: J101.A5 (CC1), R119.1
/Alimentación, carga y batería/CC2: J101.B5 (CC2), R120.1
/Alimentación, carga y batería/CHG_BATP: R107.2, U102.18 (BATP)
/Alimentación, carga y batería/CHG_BTST1: C101.1, U102.4 (BTST1)
/Alimentación, carga y batería/CHG_BTST2: C102.1, U102.19 (BTST2)
/Alimentación, carga y batería/CHG_ILIM: R101.2, R102.1, U102.17 (ILIM_HIZ)
/Alimentación, carga y batería/CHG_PROG: R103.1, U102.20 (PROG)
/Alimentación, carga y batería/CHG_SDRV: Q101.1 (G), U102.24 (SDRV)
/Alimentación, carga y batería/CHG_SW1: C101.2, L101.1, U102.28 (SW1)
/Alimentación, carga y batería/CHG_SW2: C102.2, L101.2, U102.26 (SW2)
/Alimentación, carga y batería/FG_VDD: C114.1, R112.2, R114.2, U103.3 (VDD)
/Alimentación, carga y batería/PMID: C106.1, C107.1, C108.1, U102.29 (PMID)
/Alimentación, carga y batería/REGN: C103.1, R101.1, R104.1, U102.5 (REGN)
/Alimentación, carga y batería/VBATT_IN: J102.3, J102.4, Q102.3 (D), R110.1
/Alimentación, carga y batería/VBAT_CHG: C113.1, Q101.2 (S), U102.22 (BAT), U102.23 (BAT)
/Alimentación, carga y batería/VBUS: C104.1, C105.1, D101.1 (K), J101.A4 (VBUS), J101.A9 (VBUS), J101.B4 (VBUS), J101.B9 (VBUS), U102.2 (VBUS), U102.3 (VBUS), U102.8 (VAC2), U102.9 (VAC1)
/Alimentación, carga y batería/VPACK: Q101.3 (D), Q102.2 (S), R107.1, R109.1, R112.1, U103.2 (CELL)
BTN_N: U102.12 (~QON); also elsewhere on the board
CHG_INT_N: R108.2, U102.21 (~INT); also elsewhere on the board
CHG_TS: R104.2, R105.1, U102.16 (TS); also elsewhere on the board
FG_ALRT_N: R113.2, U103.5 (~ALRT); also elsewhere on the board
I2C_SCL: U102.14 (SCL), U103.7 (SCL); also elsewhere on the board
I2C_SDA: U102.15 (SDA), U103.8 (SDA); also elsewhere on the board
USB_DN: J101.A7 (D-), J101.B7 (D-), U101.1 (I/O1), U101.6 (I/O1); also elsewhere on the board
USB_DP: J101.A6 (D+), J101.B6 (D+), U101.3 (I/O2), U101.4 (I/O2); also elsewhere on the board
VSYS: C109.1, C110.1, C111.1, C112.1, C115.1, C116.1, R115.1, U102.25 (SYS), U105.6 (VIN); also elsewhere on the board

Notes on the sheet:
Entrada USB-C (5 V sin PD, datos al ESP32)
Cargador BQ25798 (buck-boost NVDC, 1S por defecto; 2S por PROG)
Batería: polaridad inversa, FET de apagado (ship) y medidor
3.3 V: TPS62903 (3-17 V, 3 A, modo 100 %)
Banderas de alimentación (ERC)
J102 (GH 4, dos contactos por polo): el pack necesita cable GH de 4 hilos AWG 26; ICHG del BQ25798 <= 1.5 A.

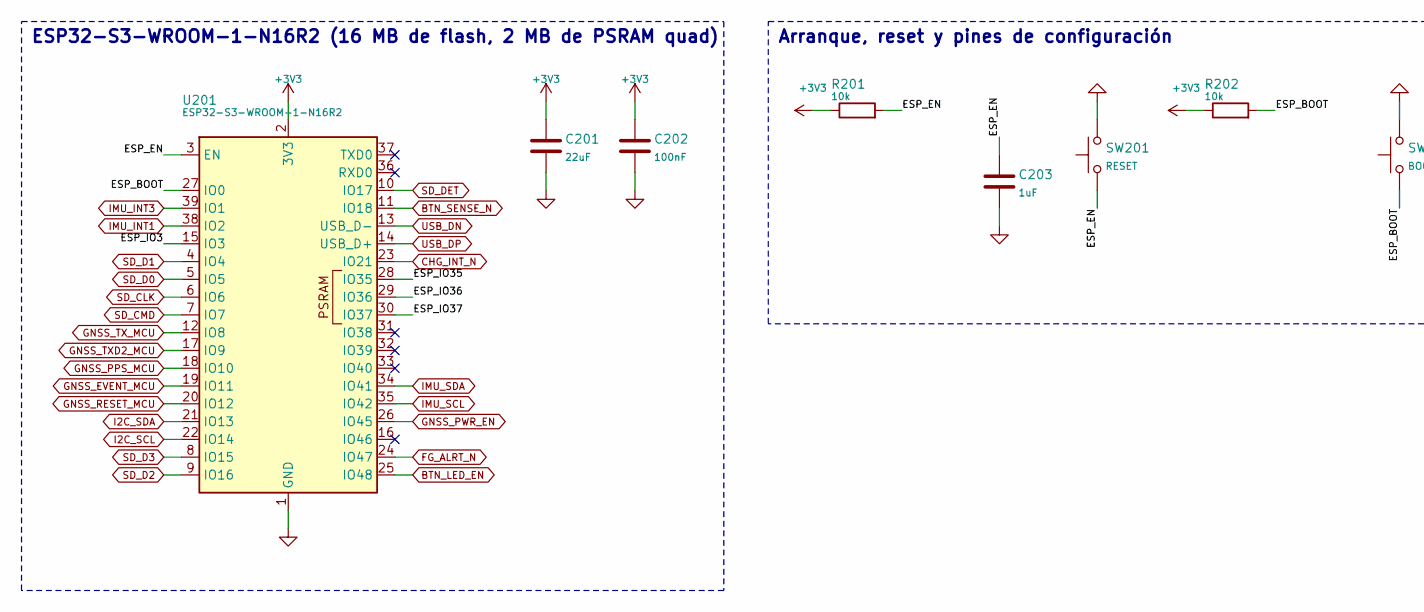
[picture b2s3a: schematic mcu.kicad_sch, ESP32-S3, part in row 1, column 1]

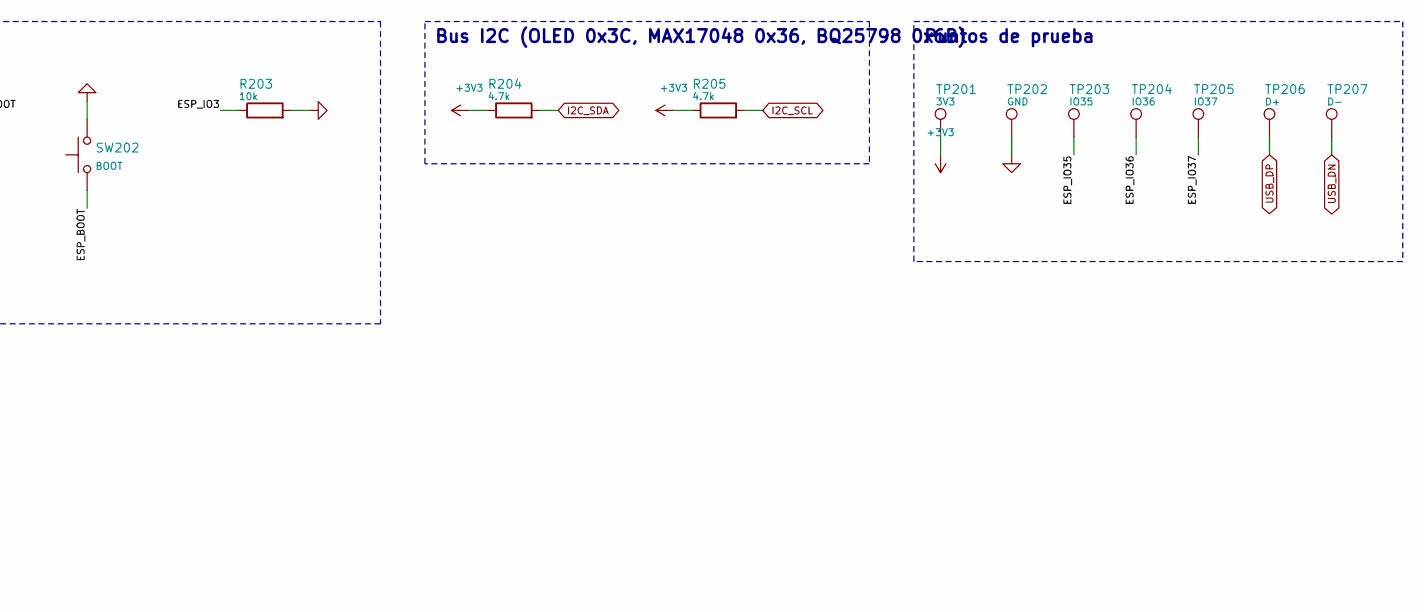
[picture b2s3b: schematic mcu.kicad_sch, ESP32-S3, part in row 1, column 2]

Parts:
C201: 22uF; C_0805_2012Metric; MPN CL21A226MAQNNNE; LCSC C45783
C202: 100nF; C_0402_1005Metric; MPN CL05B104KB54PNC; LCSC C307331
C203: 1uF; C_0402_1005Metric; MPN CL05A105KA5NQNC; LCSC C52923
R201, R202, R203: 10k; R_0402_1005Metric; MPN 0402WGF1002TCE; LCSC C25744
R204, R205: 4.7k; R_0402_1005Metric; MPN 0402WGF4701TCE; LCSC C25900
SW201: RESET; SW-SMD_L3.9-W3.0-P4.45; MPN TS-1088-AR02016; LCSC C720477
SW202: BOOT; SW-SMD_L3.9-W3.0-P4.45; MPN TS-1088-AR02016; LCSC C720477
TP201: 3V3; TestPoint_Pad_D1.0mm
TP202: GND; TestPoint_Pad_D1.0mm
TP203: IO35; TestPoint_Pad_D1.0mm
TP204: IO36; TestPoint_Pad_D1.0mm
TP205: IO37; TestPoint_Pad_D1.0mm
TP206: D+; TestPoint_Pad_D1.0mm
TP207: D-; TestPoint_Pad_D1.0mm
U201: ESP32-S3-WROOM-1-N16R2; WIRELM-SMD_ESP32-S3-WROOM-1; MPN ESP32-S3-WROOM-1-N16R2; LCSC C2913205

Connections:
/ESP32-S3/ESP_BOOT: R202.2, SW202.1, U201.27 (IO0)
/ESP32-S3/ESP_EN: C203.1, R201.2, SW201.1, U201.3 (EN)
/ESP32-S3/ESP_IO3: R203.1, U201.15 (IO3)
/ESP32-S3/ESP_IO35: TP203.1, U201.28 (IO35)
/ESP32-S3/ESP_IO36: TP204.1, U201.29 (IO36)
/ESP32-S3/ESP_IO37: TP205.1, U201.30 (IO37)
/ESP32-S3/ESP_RXD0: U201.36 (RXD0); also elsewhere on the board
/ESP32-S3/ESP_TXD0: U201.37 (TXD0); also elsewhere on the board
BTN_SENSE_N: U201.11 (IO18); also elsewhere on the board
CHG_INT_N: U201.23 (IO21); also elsewhere on the board
FG_ALRT_N: U201.24 (IO47); also elsewhere on the board
GNSS_EVENT_MCU: U201.19 (IO11); also elsewhere on the board
GNSS_PPS_MCU: U201.18 (IO10); also elsewhere on the board
GNSS_PWR_EN: U201.26 (IO45); also elsewhere on the board
GNSS_RESET_MCU: U201.20 (IO12); also elsewhere on the board
GNSS_TXD2_MCU: U201.17 (IO9); also elsewhere on the board
GNSS_TX_MCU: U201.12 (IO8); also elsewhere on the board
I2C_SCL: R205.2, U201.22 (IO14); also elsewhere on the board
I2C_SDA: R204.2, U201.21 (IO13); also elsewhere on the board
IMU_INT1: U201.38 (IO2); also elsewhere on the board
IMU_INT3: U201.39 (IO1); also elsewhere on the board
IMU_SCL: U201.35 (IO42); also elsewhere on the board
IMU_SDA: U201.34 (IO41); also elsewhere on the board
SD_CLK: U201.6 (IO6); also elsewhere on the board
SD_CMD: U201.7 (IO7); also elsewhere on the board
SD_D0: U201.5 (IO5); also elsewhere on the board
SD_D1: U201.4 (IO4); also elsewhere on the board
SD_D2: U201.9 (IO16); also elsewhere on the board
SD_D3: U201.8 (IO15); also elsewhere on the board
SD_DET: U201.10 (IO17); also elsewhere on the board
USB_DN: TP207.1, U201.13 (USB_D-); also elsewhere on the board
USB_DP: TP206.1, U201.14 (USB_D+); also elsewhere on the board

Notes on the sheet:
ESP32-S3-WROOM-1-N16R2 (16 MB de flash, 2 MB de PSRAM quad)
Arranque, reset y pines de configuración
Bus I2C (OLED 0x3C, MAX17048 0x36, BQ25798 0x6B)
Puntos de prueba
